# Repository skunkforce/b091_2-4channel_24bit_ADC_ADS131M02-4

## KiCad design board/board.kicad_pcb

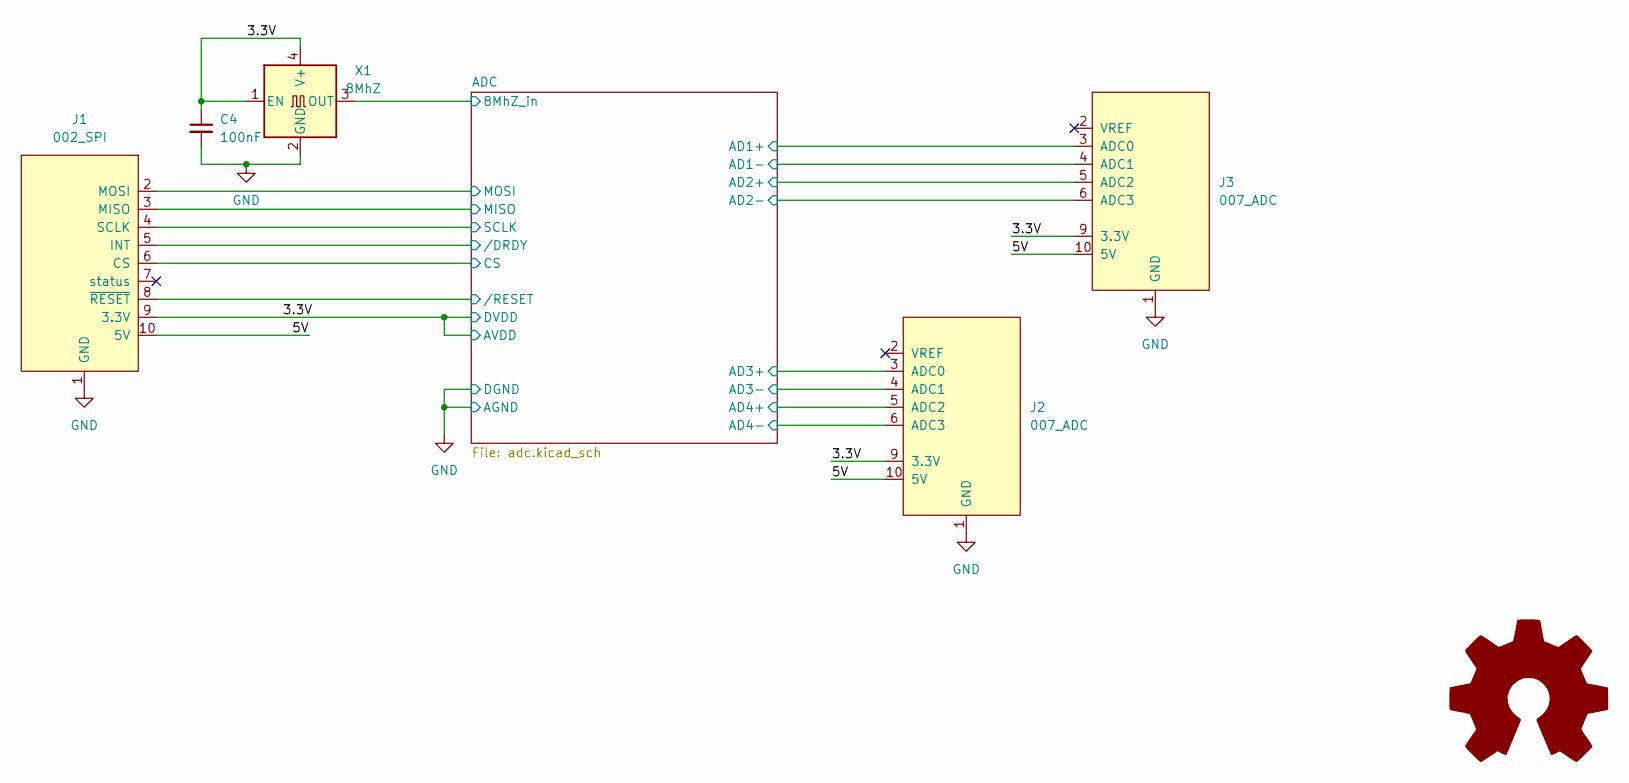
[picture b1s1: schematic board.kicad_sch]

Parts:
C4: 100nF; C_0603_1608Metric
J1: 002_SPI; on_edge_2x05_device
J2, J3: 007_ADC; on_edge_2x05_host
X1: 8MhZ; Oscillator_SMD_EuroQuartz_XO32-4Pin_3.2x2.5mm; MPN O 8,0-JO32-B-1V3-1-T1-LF
l1: Logo_Open_Hardware_Larg; OSHW-Logo2_7.3x6mm_SilkScreen

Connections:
/3.3V: C4.1, J1.9 (3.3V), J2.9 (3.3V), J3.9 (3.3V), X1.1 (EN), X1.4 (V+); also elsewhere on the board
/5V: J1.10 (5V), J2.10 (5V), J3.10 (5V)
/ADC/8MhZ_in: X1.3 (OUT); also elsewhere on the board
/ADC/AD1+: J3.3 (ADC0); also elsewhere on the board
/ADC/AD1-: J3.4 (ADC1); also elsewhere on the board
/ADC/AD2+: J3.5 (ADC2); also elsewhere on the board
/ADC/AD2-: J3.6 (ADC3); also elsewhere on the board
/ADC/AD3+: J2.3 (ADC0); also elsewhere on the board
/ADC/AD3-: J2.4 (ADC1); also elsewhere on the board
/ADC/AD4+: J2.5 (ADC2); also elsewhere on the board
/ADC/AD4-: J2.6 (ADC3); also elsewhere on the board
/ADC/CS: J1.6 (CS); also elsewhere on the board
/ADC/MISO: J1.3 (MISO); also elsewhere on the board
/ADC/MOSI: J1.2 (MOSI); also elsewhere on the board
/ADC/SCLK: J1.4 (SCLK); also elsewhere on the board
/ADC//DRDY: J1.5 (INT); also elsewhere on the board
/ADC//RESET: J1.8 (~RESET); also elsewhere on the board
GND: C4.2, J1.1 (GND), J2.1 (GND), J3.1 (GND), X1.2 (GND); also elsewhere on the board

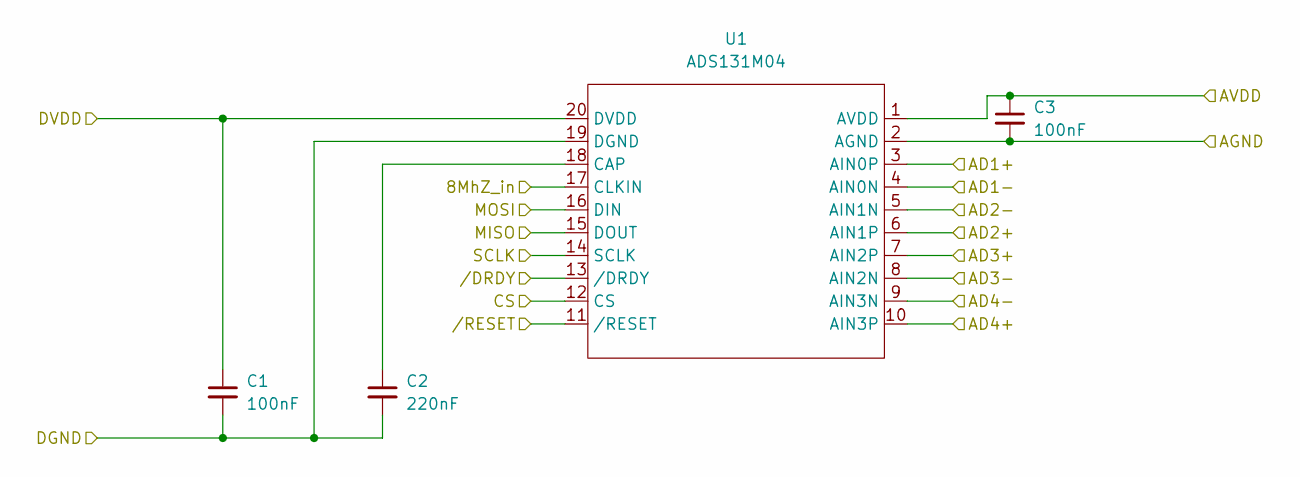
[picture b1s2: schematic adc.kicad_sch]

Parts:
C1, C3: 100nF; C_0603_1608Metric
C2: 220nF; C_0603_1608Metric
U1: ADS131M04; TSSOP-20_4.4x6.5mm_P0.65mm

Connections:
/3.3V: C1.1, C3.1, U1.1 (AVDD), U1.20 (DVDD); also elsewhere on the board
/ADC/8MhZ_in: U1.17 (CLKIN); also elsewhere on the board
/ADC/AD1+: U1.3 (AIN0P); also elsewhere on the board
/ADC/AD1-: U1.4 (AIN0N); also elsewhere on the board
/ADC/AD2+: U1.6 (AIN1P); also elsewhere on the board
/ADC/AD2-: U1.5 (AIN1N); also elsewhere on the board
/ADC/AD3+: U1.7 (AIN2P); also elsewhere on the board
/ADC/AD3-: U1.8 (AIN2N); also elsewhere on the board
/ADC/AD4+: U1.10 (AIN3P); also elsewhere on the board
/ADC/AD4-: U1.9 (AIN3N); also elsewhere on the board
/ADC/CS: U1.12 (CS); also elsewhere on the board
/ADC/MISO: U1.15 (DOUT); also elsewhere on the board
/ADC/MOSI: U1.16 (DIN); also elsewhere on the board
/ADC/SCLK: U1.14 (SCLK); also elsewhere on the board
/ADC//DRDY: U1.13 (/DRDY); also elsewhere on the board
/ADC//RESET: U1.11 (/RESET); also elsewhere on the board
GND: C1.2, C2.2, C3.2, U1.2 (AGND), U1.19 (DGND); also elsewhere on the board
unnamed: C2.1, U1.18 (CAP)

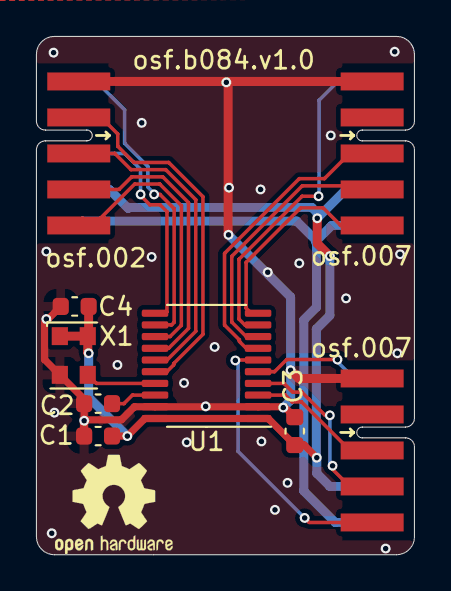
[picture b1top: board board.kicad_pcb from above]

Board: 2 copper layers, 21.0 x 28.8 mm, 10 parts (0 on the bottom side), 19 nets.

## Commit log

2023-12-11 initial
2023-12-12 added docs
